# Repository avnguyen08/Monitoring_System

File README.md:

# Current Monitoring System 

Various current monitoring software products made on the ESP32 using varied electronic components including: LCDs, external ADC, potentiometers, capacitors, resistors, plug-and-play connectors, and 7 segment displays

### Version A (7-Segment Display)
ESP32 Feather Board paired with a Featherwing 7-Segment Display to display the amount of amps passing through a material and the amount of time the amps passed through for. The external ADC can handle voltage bursts as low as 2mv at 180 ms 
- Language: C++
 - Components: ESP32 Feather, external ADC, 7-segment display featherwing, LEDs, potentiometers, capacitors, resistors, socket connectors, pin head connectors, 5V power adapter.
- Description:
    Cycles between displaying the current and time on a 7-Segment display. Display times are customizable using potentiometers on back of PCB
    External pull down resistors and decoupling cacpacitors used for signal integrity.
    Dip switch in back to provide customizability with regard to different shunts and machines. 
    Machines operate at thousands of current and use a shunt to have readable levels, ranging from 2mv to 4V. 
    Pin headers and socket headers for easy installation into varied machines.

### Version B (LCD Display)
- Language: C++
- Components: LilyGo T Display S3, external ADC, capacitors, resistors, socket connectors, pin head connectors, 5V power adapter.
- Description: 
  Communication with LCD using SPI. Communication with external ADC using I2C. ESP32 simulatenously displays the amount of amps passing through a material and the amount of time the amps passed through for. Decoupling Capacitors and pull down resistors used for signal integrety. Pin headers and 
  socket headers for easy installation into varied machines.

### Version C (LCD Display + Hardware Filter)
 - Language: C++
 - Components: LilyGo T Display S3, external ADC, capacitors, resistors, socket connectors, pin head connectors, 5V power adapter, op amps, potentiometers.
 - Description: Communication with LCD using SPI, Communication with external ADC using I2C. ESP32 simulatenously displays the amount of amps passing through a material and the amount of time the amps passed through for. Decoupling Capacitors and pull down resistors used for signal integrety. Pin headers and socket headers for easy installation into varied machines. Integrated legacy hardware filter used to help clean up dirty signals caused by electromagnetic interference.

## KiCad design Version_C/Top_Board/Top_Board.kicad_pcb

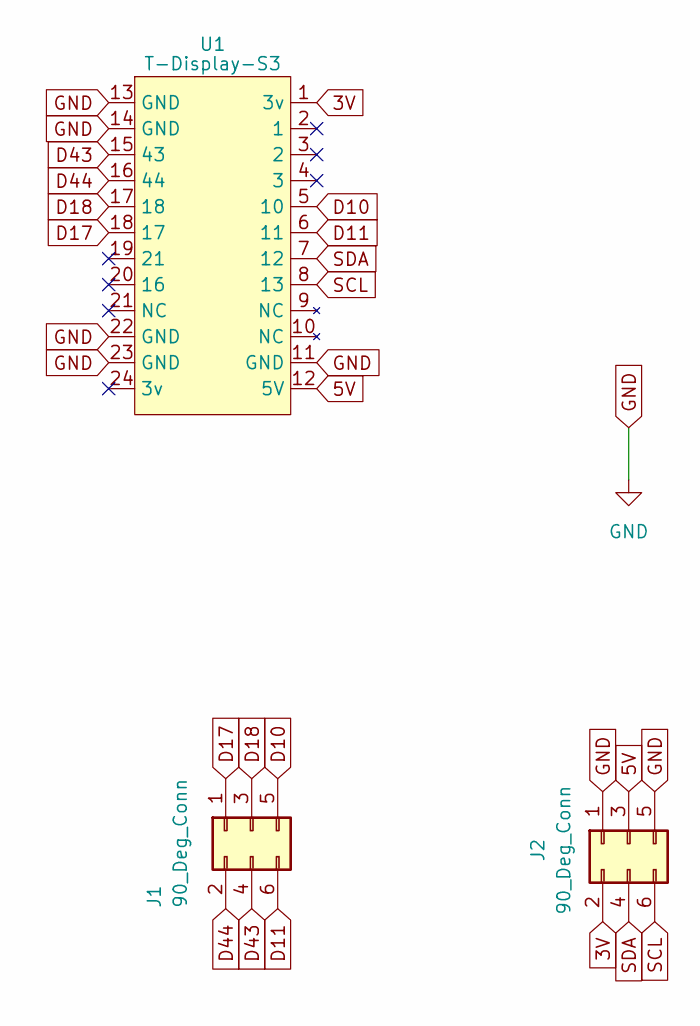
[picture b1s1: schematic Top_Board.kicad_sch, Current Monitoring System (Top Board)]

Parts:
J1, J2: 90_Deg_Conn; PinHeader_2x03_P2.54mm_Horizontal
U1: T-Display-S3

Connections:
3V: J2.2, U1.1 (3v)
5V: J2.3, U1.12 (5V)
D10: J1.5, U1.5 (10)
D11: J1.6, U1.6 (11)
D17: J1.1, U1.18 (17)
D18: J1.3, U1.17 (18)
D43: J1.4, U1.15 (43)
D44: J1.2, U1.16 (44)
GND: J2.1, J2.5, U1.11 (GND), U1.13 (GND), U1.14 (GND), U1.22 (GND), U1.23 (GND)
SCL: J2.6, U1.8 (13)
SDA: J2.4, U1.7 (12)

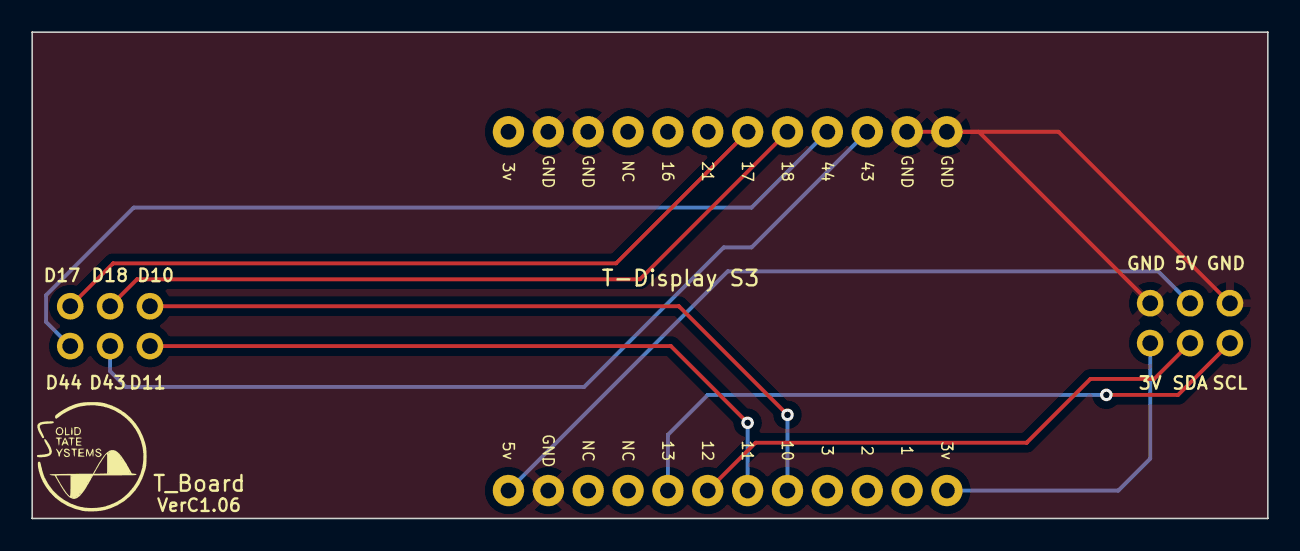
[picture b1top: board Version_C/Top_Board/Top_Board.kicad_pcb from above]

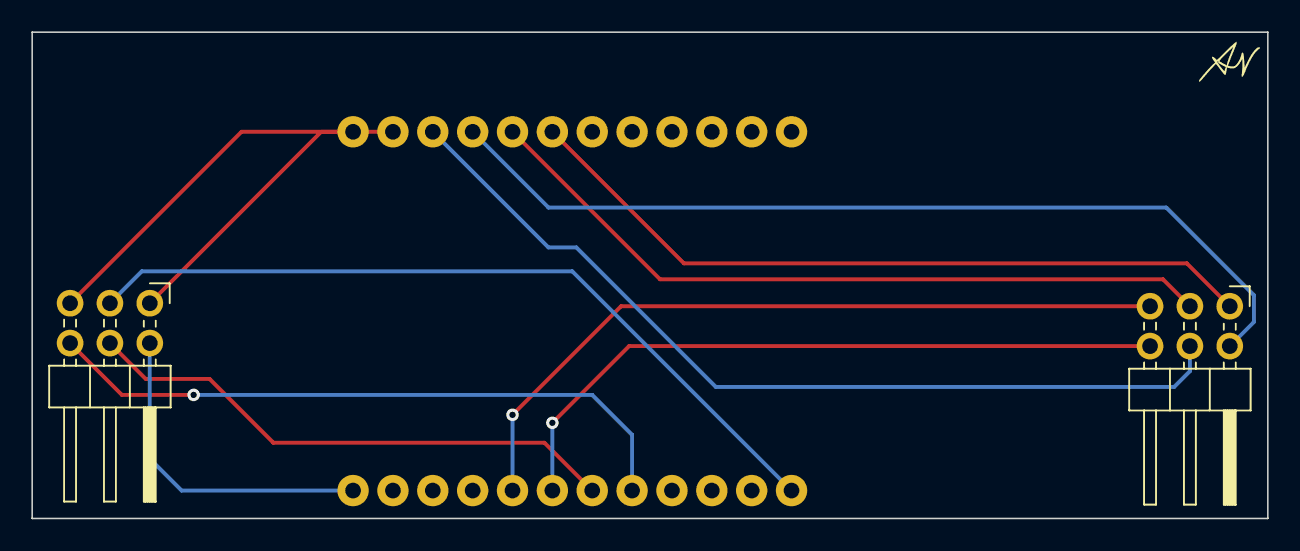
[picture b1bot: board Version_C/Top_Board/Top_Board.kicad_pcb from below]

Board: 2 copper layers, 78.7 x 31.0 mm, 3 parts (2 on the bottom side), 11 nets.

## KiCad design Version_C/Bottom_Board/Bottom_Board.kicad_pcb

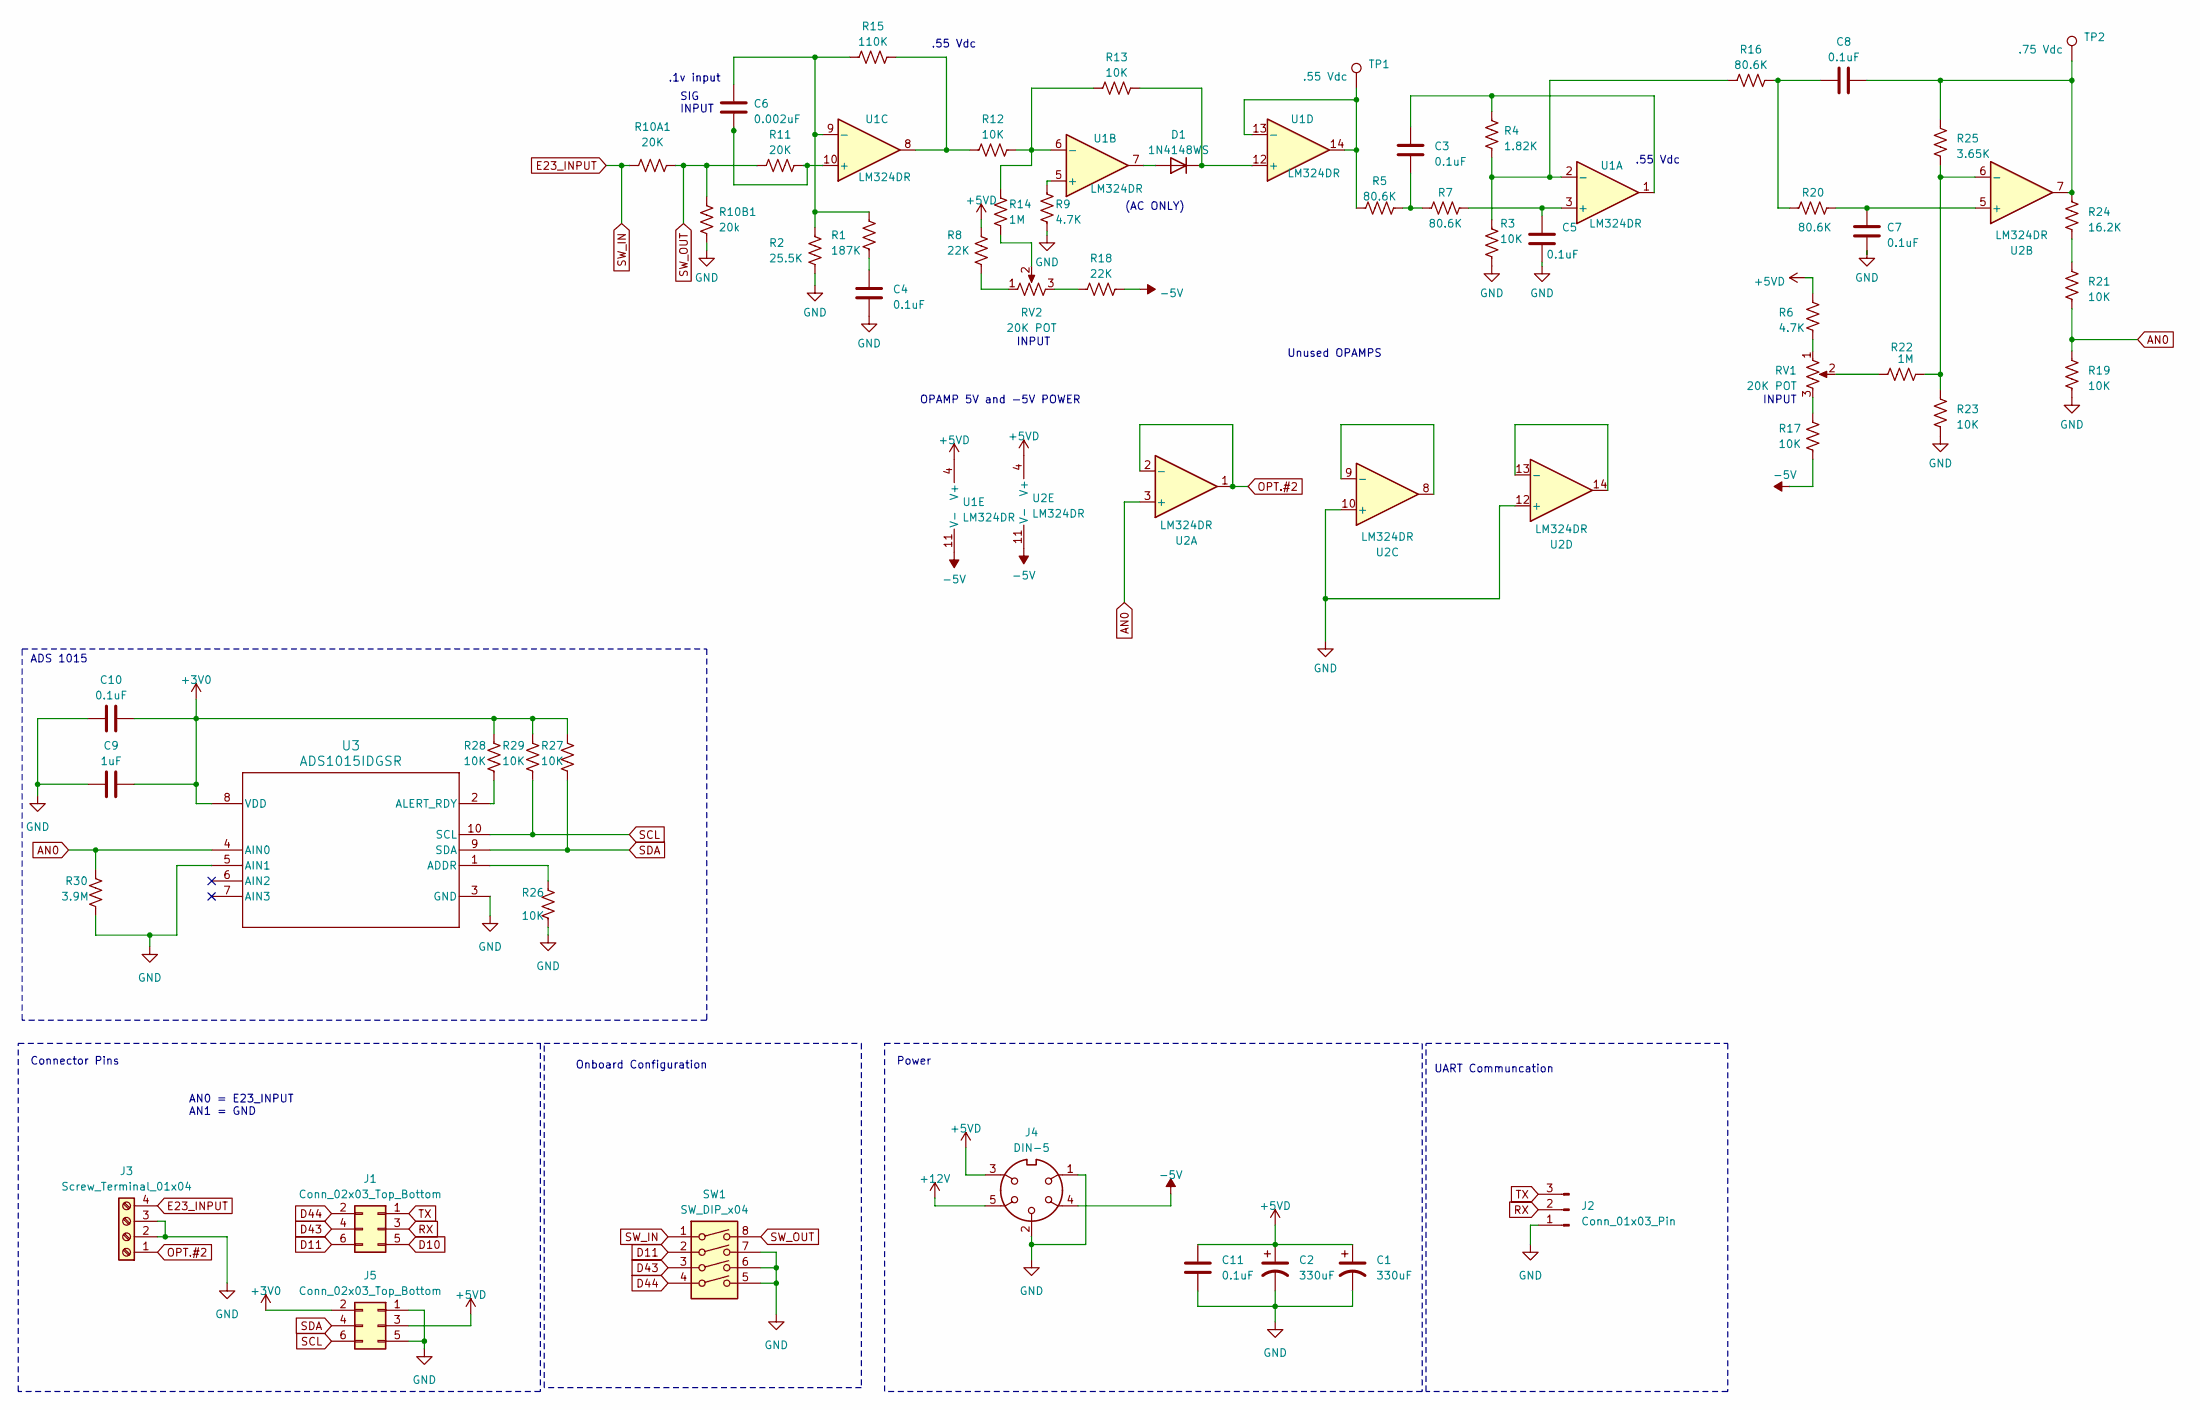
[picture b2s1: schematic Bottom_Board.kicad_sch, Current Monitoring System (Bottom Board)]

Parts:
C1, C2: 330uF; CP_Radial_D10.0mm_P5.00mm
C3, C4, C5, C7, C8, C10, C11: 0.1uF; C_0603_1608Metric
C6: 0.002uF; C_0603_1608Metric
C9: 1uF; C_0603_1608Metric
D1: 1N4148WS; Diode_1N4148WS
J1, J5: Conn_02x03_Top_Bottom; PinSocket_2x03_P2.54mm_Vertical
J2: Conn_01x03_Pin; PinHeader_1x03_P2.54mm_Vertical
J3: Screw_Terminal_01x04; Terminal_Strip_4_Pin
J4: DIN-5; DIN_5_PIN
R1: 187K; R_0603_1608Metric
R2: 25.5K; R_0603_1608Metric
R3, R12, R13, R17, R19, R21, R23, R26, R27, R28, R29: 10K; R_0603_1608Metric
R4: 1.82K; R_0603_1608Metric
R5, R7, R16, R20: 80.6K; R_0603_1608Metric
R6, R9: 4.7K; R_0603_1608Metric
R8, R18: 22K; R_0603_1608Metric
R10A1, R11: 20K; R_0603_1608Metric
R10B1: 20k; R_0603_1608Metric
R14, R22: 1M; R_0603_1608Metric
R15: 110K; R_0603_1608Metric
R24: 16.2K; R_0603_1608Metric
R25: 3.65K; R_0603_1608Metric
R30: 3.9M; R_0603_1608Metric
RV1, RV2: 20K POT; Potentiometer_Bourns_3386P_Vertical
SW1: SW_DIP_x04; SW_DIP_SPSTx04_Slide_9.78x12.34mm_W7.62mm_P2.54mm
TP1: .55 Vdc; TestPoint_Loop_D2.54mm_Drill1.5mm_Beaded
TP2: .75 Vdc; TestPoint_Loop_D2.54mm_Drill1.5mm_Beaded
U1, U2: LM324DR; SOIC-14_3.9x8.7mm_P1.27mm
U3: ADS1015IDGSR; DGS0010A_N

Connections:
+3V0: C9.2, C10.2, J5.2, R27.1, R28.1, R29.1, U3.8 (VDD)
+5VD: C1.1, C2.1, C11.1, J4.3, J5.3, R6.2, R8.1, U1.4 (V+), U2.4 (V+)
+12V: J4.5
-5V: J4.4, R17.1, R18.2, U1.11 (V-), U2.11 (V-)
AN0: R19.2, R21.1, R30.1, U2.3 (+), U3.4 (AIN0)
D10: J1.5
D11: J1.6, SW1.2
D43: J1.4, SW1.3
D44: J1.2, SW1.4
E23_INPUT: J3.4, R10A1.1, SW1.1
GND: C1.2, C2.2, C4.2, C5.2, C7.1, C9.1, C10.1, C11.2, J2.1, J3.2, J3.3, J4.1, J4.2, J5.1, J5.5, R2.2, R3.2, R9.2, R10B1.2, R19.1, R23.1, R26.2, R30.2, SW1.5, SW1.6, SW1.7, U2.10 (+), U2.12 (+), U3.3 (GND), U3.5 (AIN1)
unnamed: C3.1, R4.2, U1.1
unnamed: C3.2, R5.2, R7.1
unnamed: C4.1, R1.2
unnamed: C8.1, R24.2, R25.2, TP2.1, U2.7
unnamed: C8.2, R16.1, R20.1
unnamed: D1.2 (A), U1.7
unnamed: D1.1 (K), R13.2, U1.12 (+)
unnamed: R6.1, RV1.1
unnamed: R8.2, RV2.1
unnamed: R12.1, R15.2, U1.8
unnamed: R14.2, RV2.2
unnamed: R17.2, RV1.3
unnamed: R18.1, RV2.3
unnamed: R21.2, R24.1
unnamed: R22.2, RV1.2
unnamed: C5.1, R7.2, U1.3 (+)
unnamed: R3.1, R4.1, R16.2, U1.2 (-)
unnamed: R9.1, U1.5 (+)
unnamed: R12.2, R13.1, R14.1, U1.6 (-)
unnamed: C6.2, R11.2, U1.10 (+)
unnamed: C6.1, R1.1, R2.1, R15.1, U1.9 (-)
unnamed: R5.1, TP1.1, U1.13 (-), U1.14
unnamed: C7.2, R20.2, U2.5 (+)
unnamed: R22.1, R23.2, R25.1, U2.6 (-)
unnamed: U2.8, U2.9 (-)
unnamed: U2.13 (-), U2.14
unnamed: R26.1, U3.1 (ADDR)
unnamed: R28.2, U3.2 (ALERT_RDY)
OPT.#2: J3.1, U2.1, U2.2 (-)
RX: J1.3, J2.2
SCL: J5.6, R29.2, U3.10 (SCL)
SDA: J5.4, R27.2, U3.9 (SDA)
SW_OUT: R10A1.2, R10B1.1, R11.1, SW1.8
TX: J1.1, J2.3

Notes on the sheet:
Connector Pins
INPUT
.55 Vdc
AN0 = E23_INPUT AN1 = GND
Unused OPAMPS
OPAMP 5V and -5V POWER
.1v input
Power
Onboard Configuration
(AC ONLY)
SIG INPUT
ADS 1015
UART Communcation

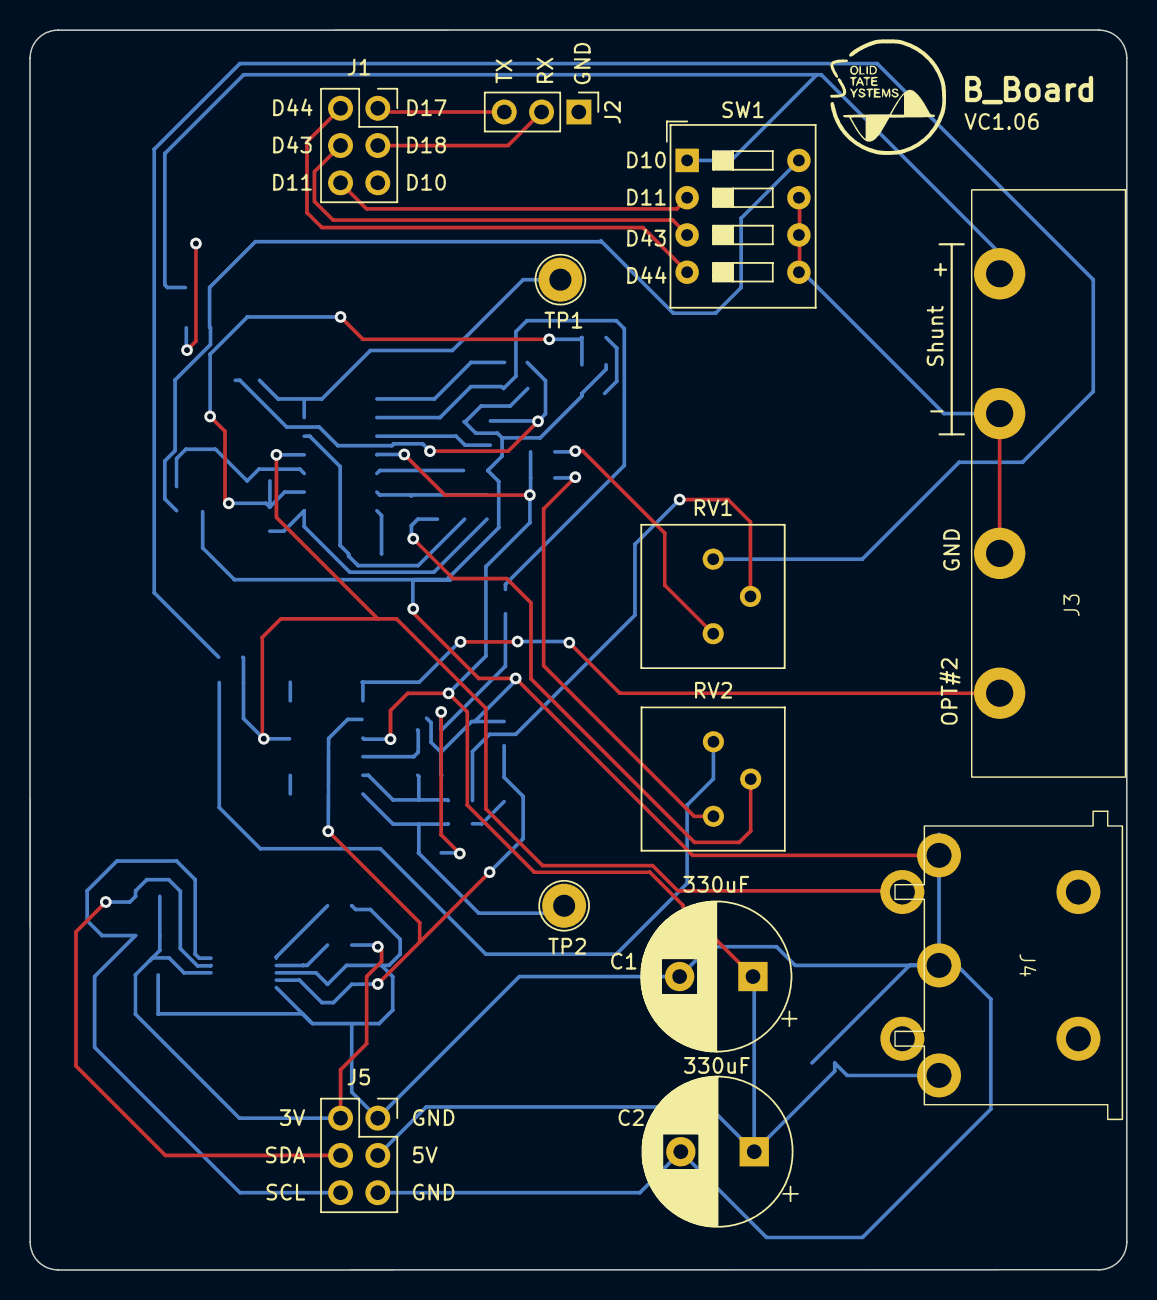
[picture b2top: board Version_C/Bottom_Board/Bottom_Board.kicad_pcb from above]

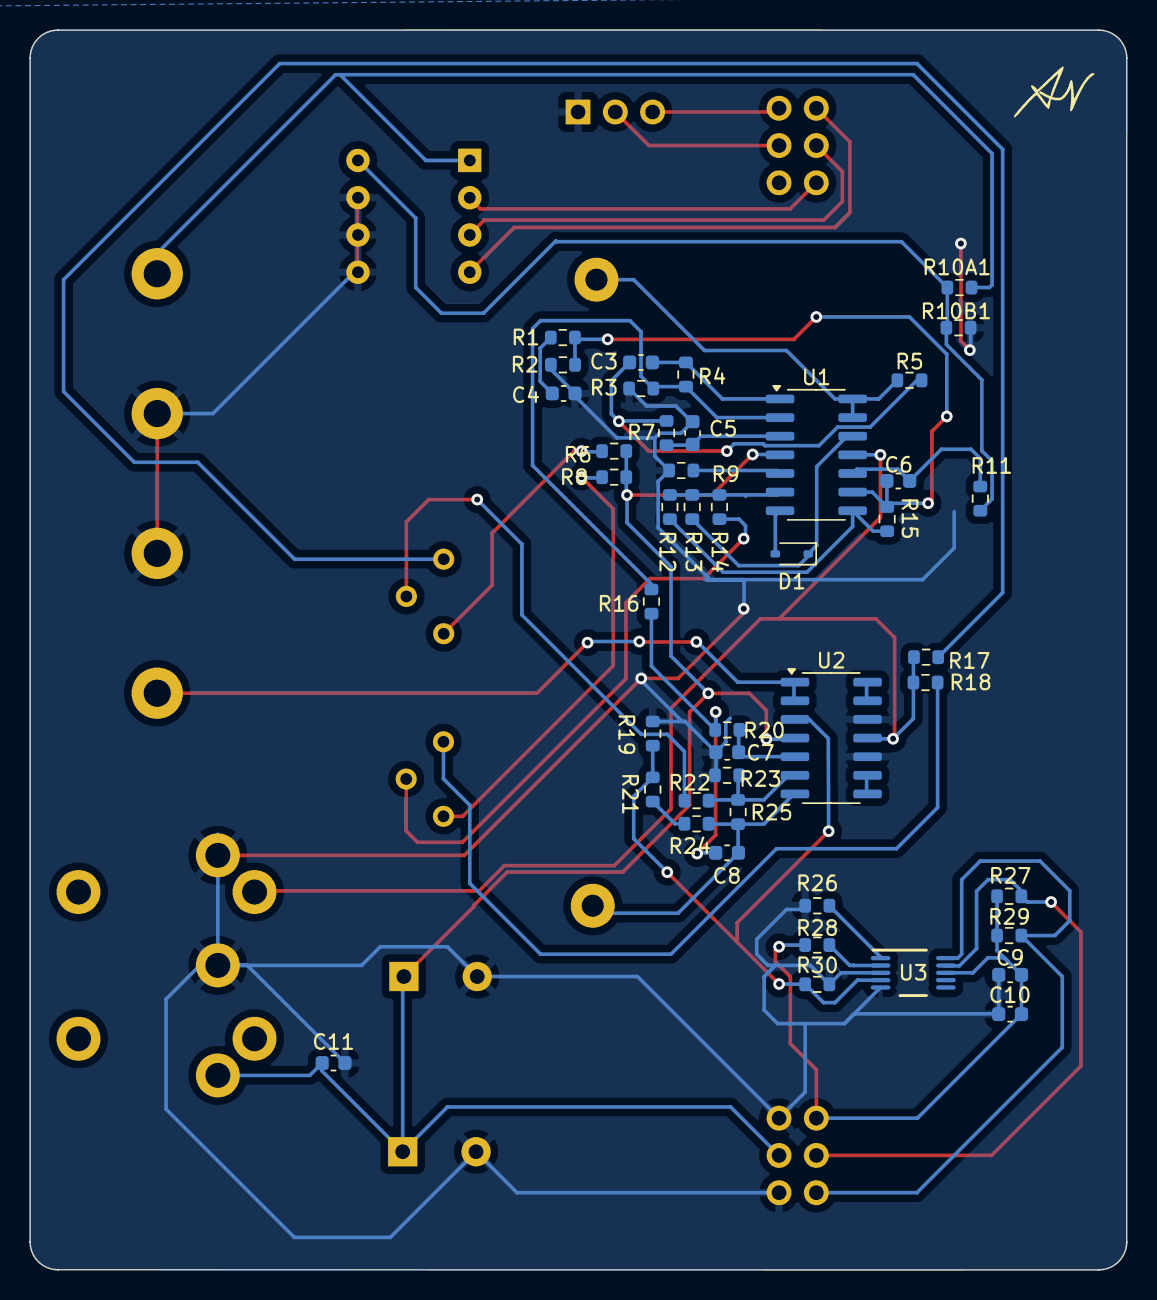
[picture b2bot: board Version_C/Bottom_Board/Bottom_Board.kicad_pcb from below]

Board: 2 copper layers, 74.8 x 84.5 mm, 56 parts (44 on the bottom side), 43 nets.

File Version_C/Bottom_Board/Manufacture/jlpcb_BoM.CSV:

Comment,Designator,Footprint
 LM324DR,"U1,U2",Package_SO:SOIC-14_3.9x8.7mm_P1.27mm
ADS1015IDGSR,U3,bot_lib:DGS0010A_N
.75 Vdc,TP2,TestPoint:TestPoint_Loop_D2.54mm_Drill1.5mm_Beaded
.55 Vdc,TP1,TestPoint:TestPoint_Loop_D2.54mm_Drill1.5mm_Beaded
SW_DIP_x04,SW1,Button_Switch_THT:SW_DIP_SPSTx04_Slide_9.78x12.34mm_W7.62mm_P2.54mm
20K POT,"RV1,RV2",bot_lib:Potentiometer_Bourns_3386P_Vertical
22K,"R8,R18",Resistor_SMD:R_0603_1608Metric
4.7K,"R6,R9",Resistor_SMD:R_0603_1608Metric
80.6K,"R5,R7,R16,R20",Resistor_SMD:R_0603_1608Metric
10K,"R3,R12,R13,R17,R19,R21,R23,R26,R27,R28,R29",Resistor_SMD:R_0603_1608Metric
1M,"R14,R22",Resistor_SMD:R_0603_1608Metric
3.9M,R30,Resistor_SMD:R_0603_1608Metric
3.65K,R25,Resistor_SMD:R_0603_1608Metric
16.2K,R24,Resistor_SMD:R_0603_1608Metric
110K,R15,Resistor_SMD:R_0603_1608Metric
20K,R11,Resistor_SMD:R_0603_1608Metric
30.1K,R10,Resistor_SMD:R_0603_1608Metric
1.82K,R4,Resistor_SMD:R_0603_1608Metric
25.5K,R2,Resistor_SMD:R_0603_1608Metric
187K,R1,Resistor_SMD:R_0603_1608Metric
Conn_02x03_Top_Bottom,"J1,J5",bot_lib:PinSocket_2x03_P2.54mm_Vertical
DIN-5,J4,bot_lib:DIN_5_PIN
Screw_Terminal_01x04,J3,bot_lib:Terminal_Strip_4_Pin
Conn_01x03_Pin,J2,Connector_PinHeader_2.54mm:PinHeader_1x03_P2.54mm_Vertical
1N4148WS,D1,bot_lib:Diode_1N4148WS
0.1uF,"C3,C4,C5,C7,C8,C10,C11",Capacitor_SMD:C_0603_1608Metric
330uF,"C1,C2",Capacitor_THT:CP_Radial_D10.0mm_P5.00mm
1uF,C9,Capacitor_SMD:C_0603_1608Metric
0.002uF,C6,Capacitor_SMD:C_0603_1608Metric

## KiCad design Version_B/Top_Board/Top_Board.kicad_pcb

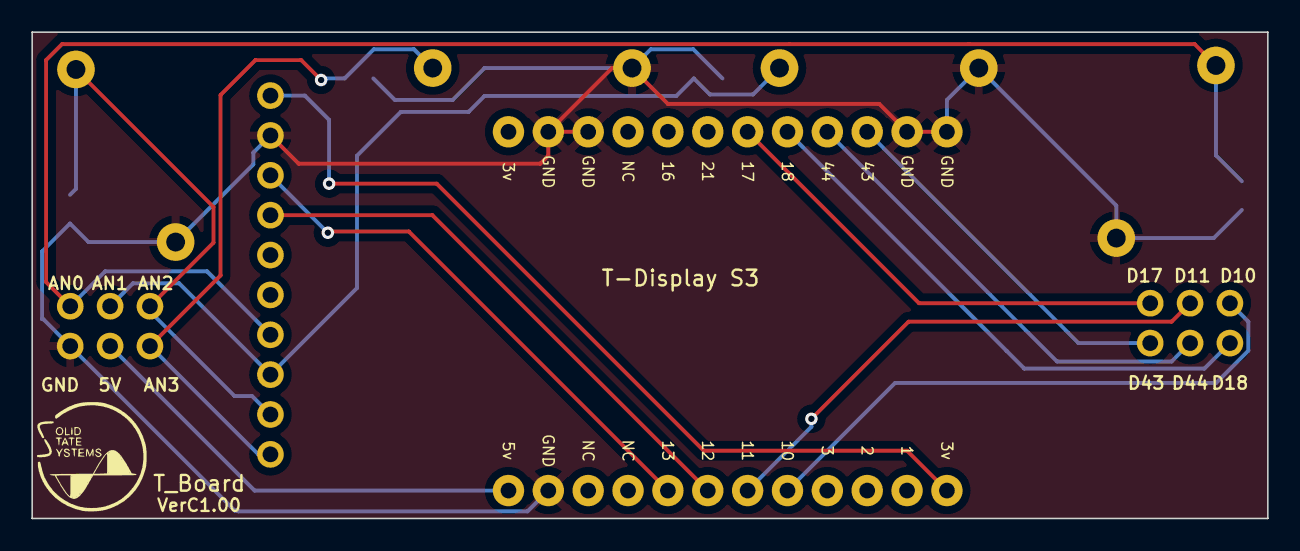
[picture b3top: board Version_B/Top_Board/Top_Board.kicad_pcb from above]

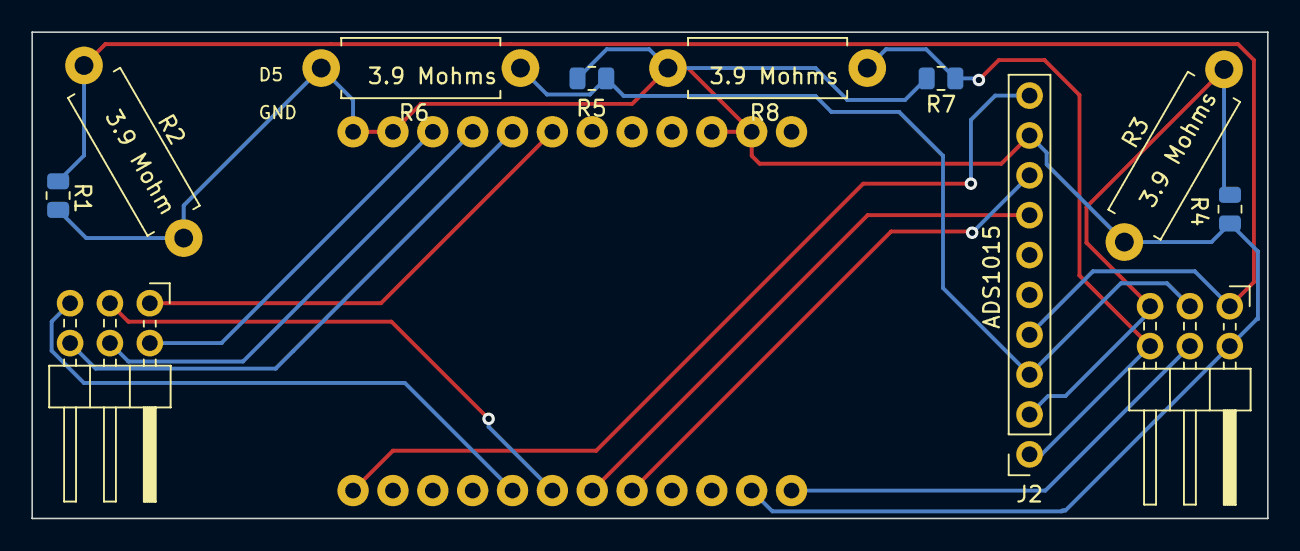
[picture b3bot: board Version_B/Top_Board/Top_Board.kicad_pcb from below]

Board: 2 copper layers, 78.7 x 31.0 mm, 12 parts (11 on the bottom side), 15 nets.

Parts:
J1, J4: 90_Deg_Conn; PinHeader_2x03_P2.54mm_Horizontal
J2: ADS1015; PinSocket_1x10_P2.54mm_Vertical_1
R1, R4, R5, R7: R; R_0805_2012Metric
R2, R3, R6, R8: R; R_Axial_DIN0411_L9.9mm_D3.6mm_P12.70mm_Horizontal
U1: T-Display-S3

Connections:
3V: J2.10, U1.1 (3v)
5V: J1.4, U1.12 (5V)
AN0: J1.1, J2.4, R1.1, R2.1
AN1: J1.3, J2.3, R5.1, R6.1
AN2: J1.5, J2.2, R3.1, R4.1
AN3: J1.6, J2.1, R7.1, R8.1
D10: J4.5, U1.5 (10)
D11: J4.3, U1.6 (11)
D17: J4.1, U1.18 (17)
D18: J4.6, U1.17 (18)
D43: J4.2, U1.15 (43)
D44: J4.4, U1.16 (44)
GND: J1.2, J2.9, R1.2, R2.2, R3.2, R4.2, R5.2, R6.2, R7.2, R8.2, U1.11 (GND), U1.13 (GND), U1.14 (GND), U1.22 (GND), U1.23 (GND)
SCL: J2.8, U1.8 (13)
SDA: J2.7, U1.7 (12)

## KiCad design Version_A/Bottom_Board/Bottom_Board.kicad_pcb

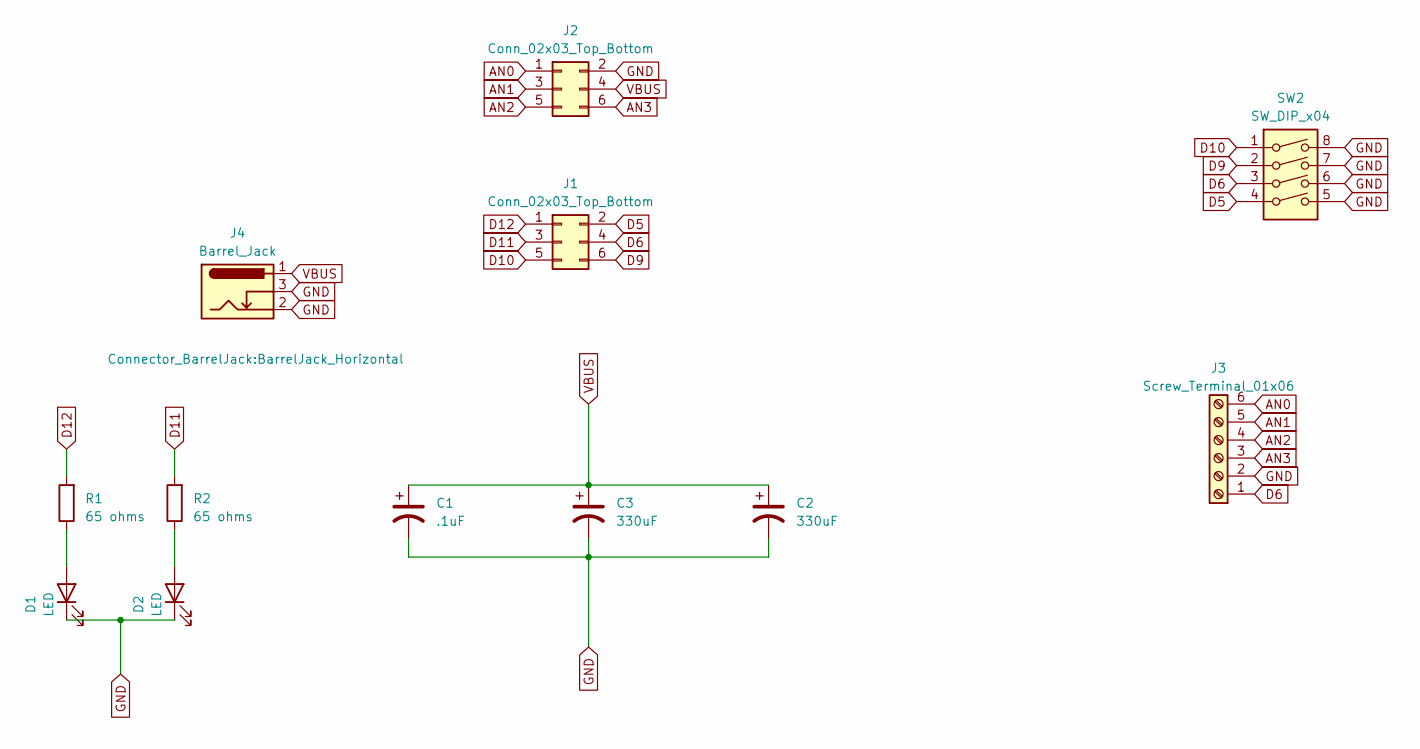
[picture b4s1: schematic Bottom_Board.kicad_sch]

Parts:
C1: .1uF; C_Disc_D3.8mm_W2.6mm_P2.50mm
C2, C3: 330uF; CP_Radial_D10.0mm_P5.00mm
D1, D2: LED; LED_D3.0mm_Horizontal_O3.81mm_Z10.0mm
J1, J2: Conn_02x03_Top_Bottom; PinSocket_2x03_P2.54mm_Vertical
J3: Screw_Terminal_01x06; PhoenixContact_MSTBA_2,5_6-G-5,08_1x06_P5.08mm_Horizontal
J4: Barrel_Jack; BarrelJack_Horizontal
R1, R2: 65 ohms; R_Axial_DIN0411_L9.9mm_D3.6mm_P12.70mm_Horizontal
SW2: SW_DIP_x04; SW_DIP_SPSTx04_Slide_9.78x12.34mm_W7.62mm_P2.54mm

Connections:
AN0: J2.1, J3.6
AN1: J2.3, J3.5
AN2: J2.5, J3.4
AN3: J2.6, J3.3
D5: J1.2, SW2.4
D6: J1.4, J3.1, SW2.3
D9: J1.6, SW2.2
D10: J1.5, SW2.1
D11: J1.3, R2.2
D12: J1.1, R1.2
GND: C1.2, C2.2, C3.2, D1.1 (K), D2.1 (K), J2.2, J3.2, J4.2, J4.3, SW2.5, SW2.6, SW2.7, SW2.8
unnamed: D1.2 (A), R1.1
unnamed: D2.2 (A), R2.1
VBUS: C1.1, C2.1, C3.1, J2.4, J4.1

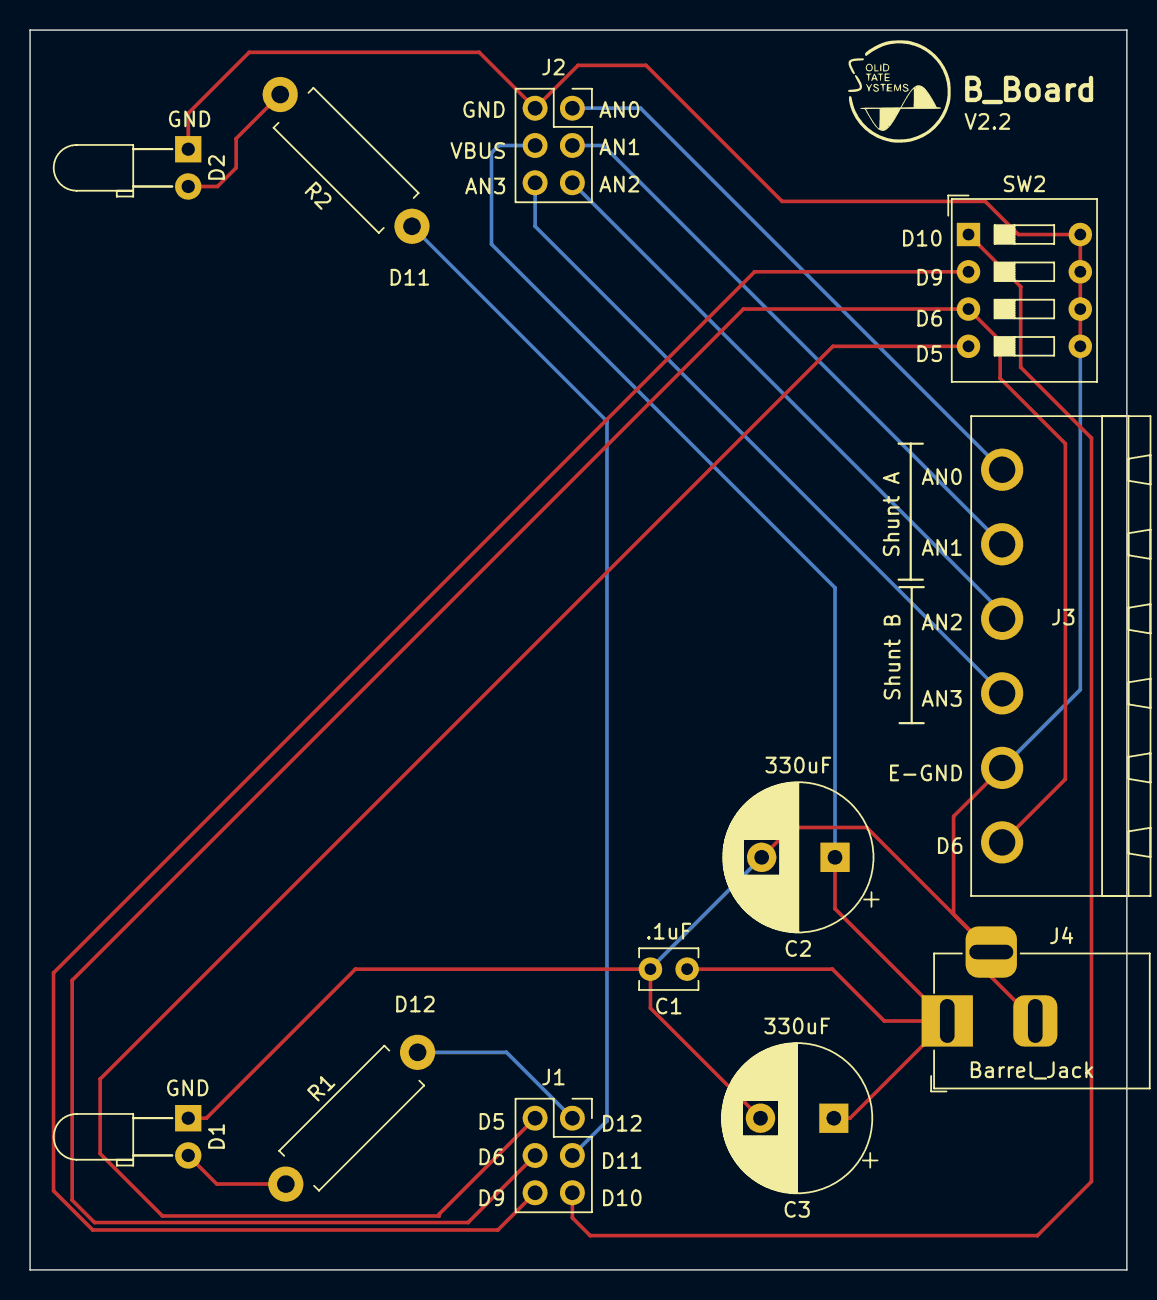
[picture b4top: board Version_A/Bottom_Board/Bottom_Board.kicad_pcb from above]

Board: 2 copper layers, 74.8 x 84.5 mm, 12 parts (0 on the bottom side), 14 nets.

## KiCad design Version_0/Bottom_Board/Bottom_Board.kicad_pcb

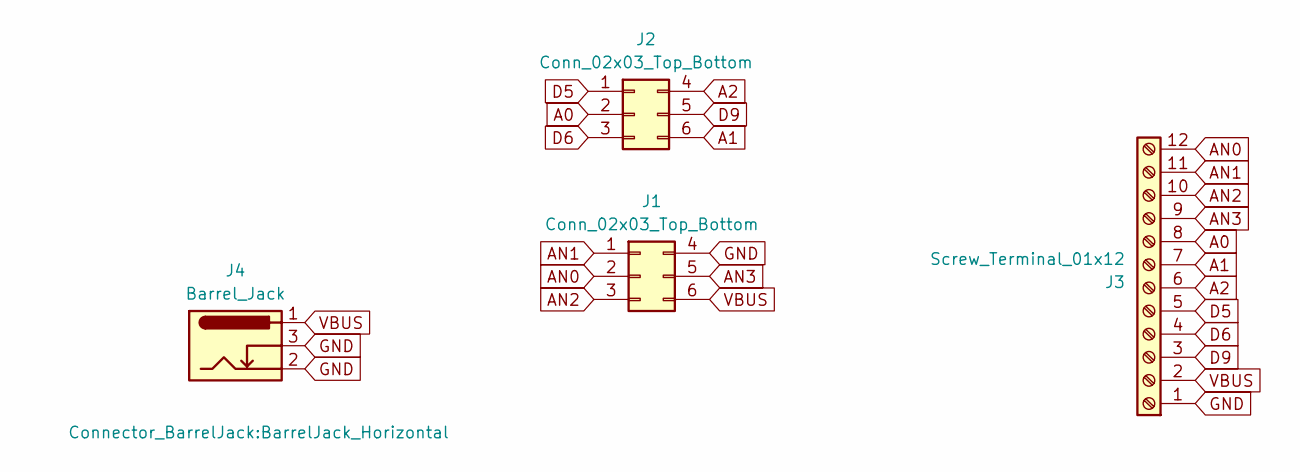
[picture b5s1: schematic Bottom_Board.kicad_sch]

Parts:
J1, J2: Conn_02x03_Top_Bottom; PinSocket_2x03_P2.54mm_Vertical
J3: Screw_Terminal_01x12; PhoenixContact_MSTBA_2,5_12-G-5,08_1x12_P5.08mm_Horizontal
J4: Barrel_Jack; BarrelJack_Horizontal

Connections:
A0: J2.2, J3.8
A1: J2.6, J3.7
A2: J2.4, J3.6
AN0: J1.2, J3.12
AN1: J1.1, J3.11
AN2: J1.3, J3.10
AN3: J1.5, J3.9
D5: J2.1, J3.5
D6: J2.3, J3.4
D9: J2.5, J3.3
GND: J1.4, J3.1, J4.2, J4.3
VBUS: J1.6, J3.2, J4.1

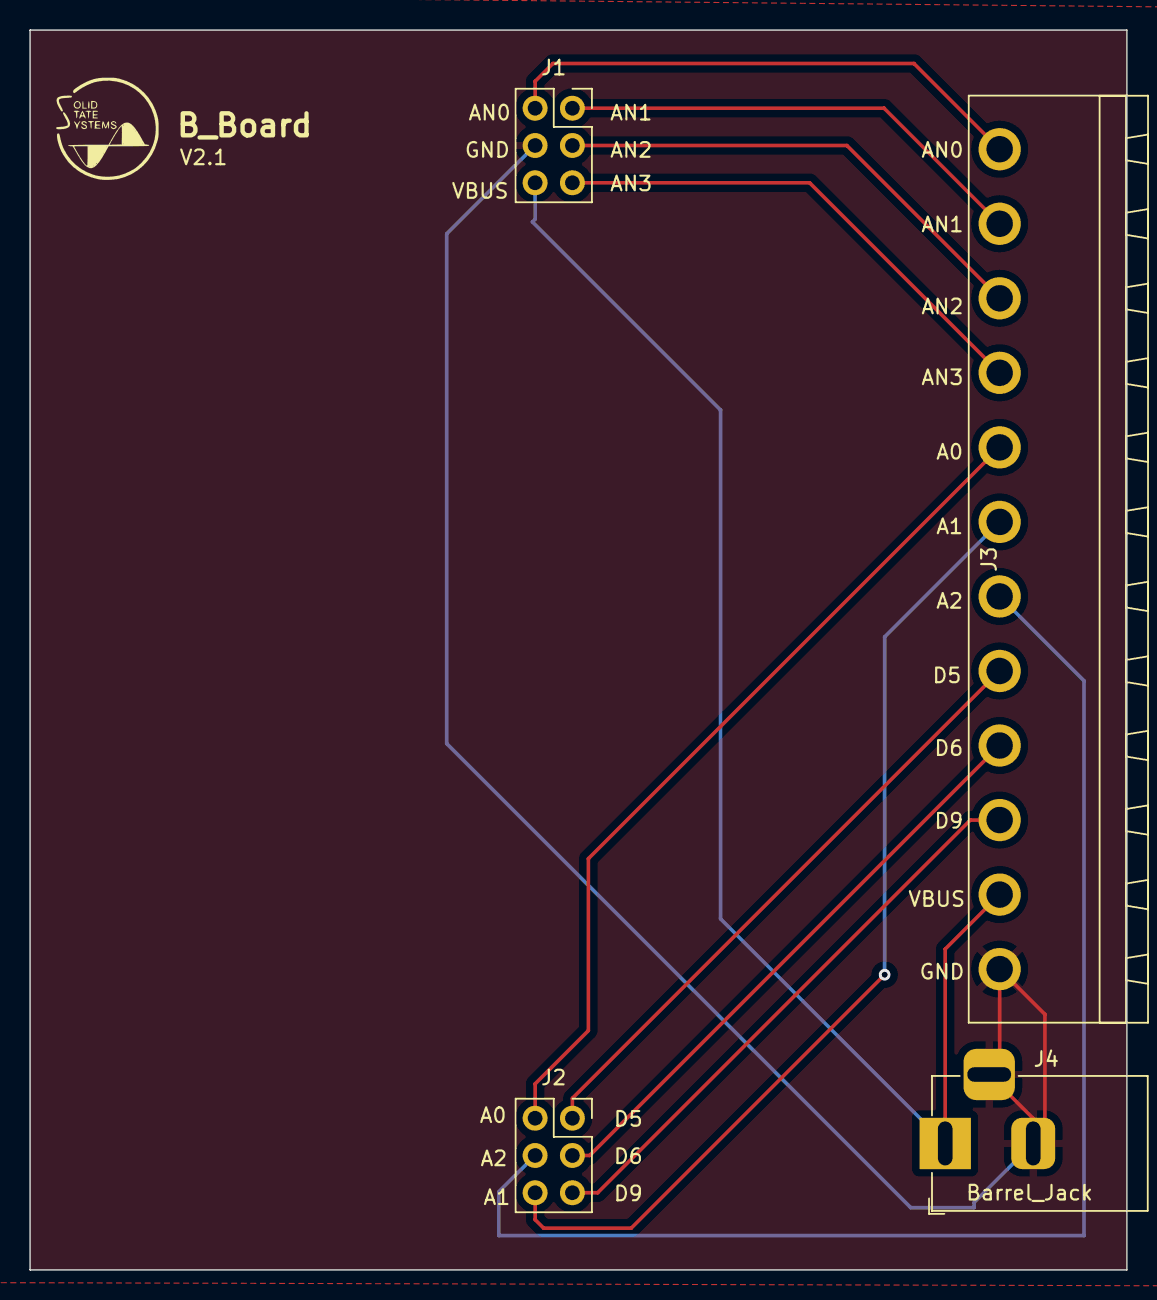
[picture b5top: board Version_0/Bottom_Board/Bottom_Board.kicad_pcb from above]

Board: 2 copper layers, 74.8 x 84.5 mm, 4 parts (0 on the bottom side), 12 nets.

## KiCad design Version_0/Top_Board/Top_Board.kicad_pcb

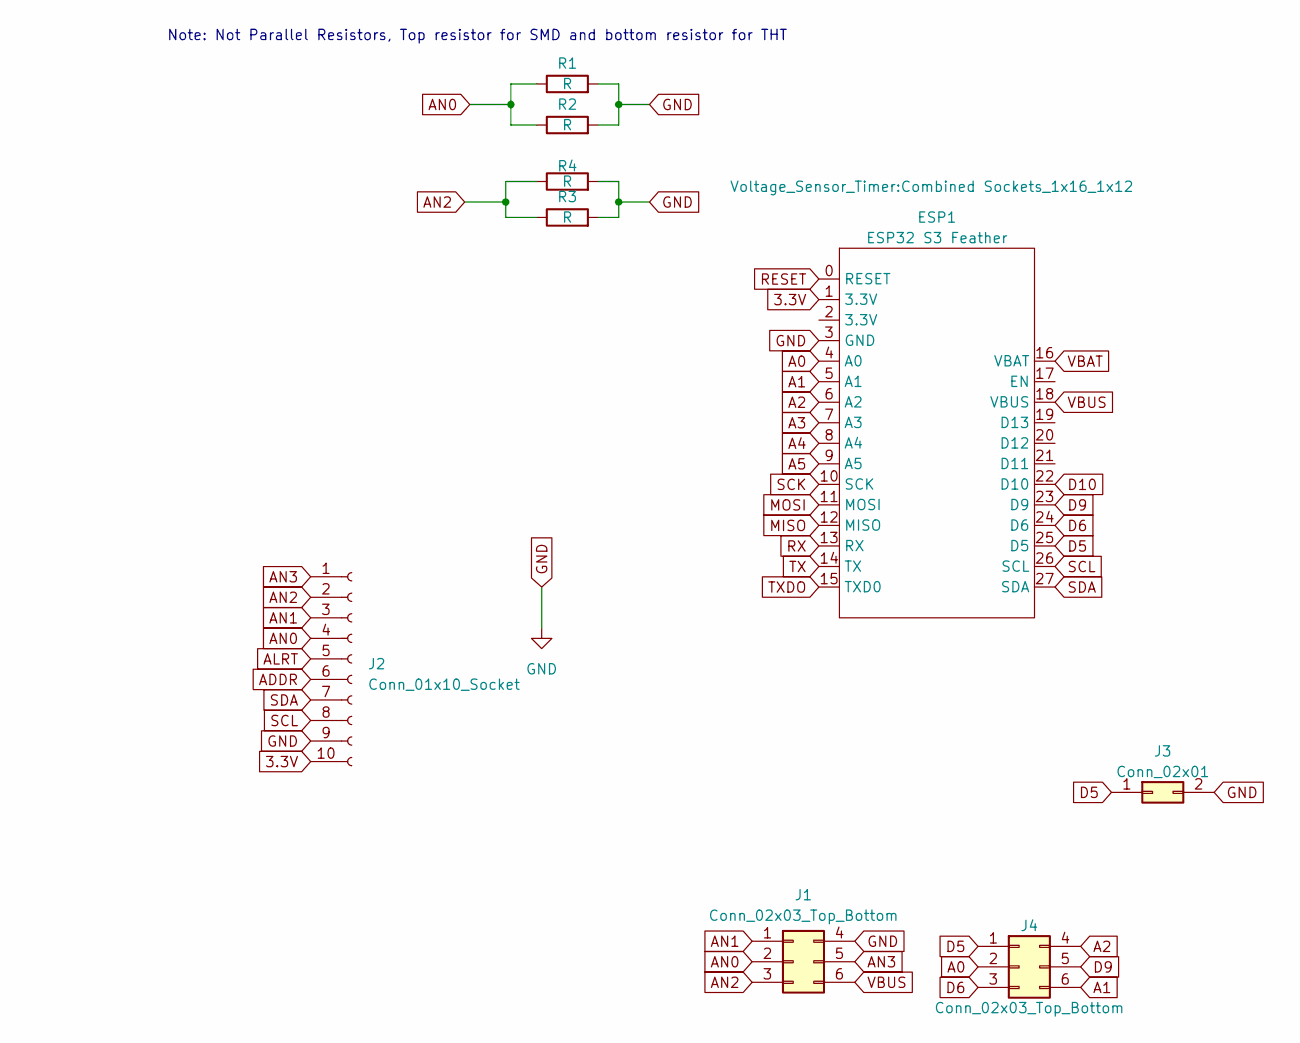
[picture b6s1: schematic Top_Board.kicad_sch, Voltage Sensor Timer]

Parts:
ESP1: ESP32 S3 Feather; Combined Sockets_1x16_1x12
J1, J4: Conn_02x03_Top_Bottom; PinHeader_2x03_P2.54mm_Horizontal
J2: Conn_01x10_Socket; PinSocket_1x10_P2.54mm_Vertical_1
J3: Conn_02x01; PinHeader_1x02_P2.54mm_Vertical
R1, R4: R; R_0805_2012Metric
R2, R3: R; R_Axial_DIN0411_L9.9mm_D3.6mm_P12.70mm_Horizontal

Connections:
3.3V: ESP1.1 (3.3V), J2.10
A0: ESP1.4 (A0), J4.2
A1: ESP1.5 (A1), J4.6
A2: ESP1.6 (A2), J4.4
A3: ESP1.7 (A3)
A4: ESP1.8 (A4)
A5: ESP1.9 (A5)
ADDR: J2.6
ALRT: J2.5
AN0: J1.2, J2.4, R1.1, R2.1
AN1: J1.1, J2.3
AN2: J1.3, J2.2, R3.1, R4.1
AN3: J1.5, J2.1
D5: ESP1.25 (D5), J3.1, J4.1
D6: ESP1.24 (D6), J4.3
D9: ESP1.23 (D9), J4.5
D10: ESP1.22 (D10)
GND: ESP1.3 (GND), J1.4, J2.9, J3.2, R1.2, R2.2, R3.2, R4.2
MISO: ESP1.12 (MISO)
MOSI: ESP1.11 (MOSI)
RESET: ESP1.0 (RESET)
RX: ESP1.13 (RX)
SCK: ESP1.10 (SCK)
SCL: ESP1.26 (SCL), J2.8
SDA: ESP1.27 (SDA), J2.7
TX: ESP1.14 (TX)
TXDO: ESP1.15 (TXD0)
VBAT: ESP1.16 (VBAT)
VBUS: ESP1.18 (VBUS), J1.6

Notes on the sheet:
Note: Not Parallel Resistors, Top resistor for SMD and bottom resistor for THT
